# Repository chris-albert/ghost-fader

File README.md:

# Ghost Fader

USB-MIDI-controlled volume and pan for two balanced 1/4" line channels. Balanced in, always-balanced out, one input becomes stereo automatically. Bus-powered Seeed XIAO RP2040 plus a 2x2 gain matrix of PGA2310 attenuators. Revision D: USB only, no DIN jack, no DC jack; the audio side is galvanically isolated from the computer. A TI ISO7762F carries the four control lines and two sense lines across a split in the ground pours, the DC-DC module is the only power path across it, and a 78L05 makes the PGA logic supply on the audio side. About $6 of parts on top of rev C (XIAO RP2040, Traco TBA 2-0522).

The full schematic package (block diagram, five sheets, level budget, USB power budget, MIDI map, build order) is published at https://chris-albert.github.io/ghost-fader/ (source: `docs/index.html`). This file is the short version.

## Signal chain

```
J1/J2 TRS in -> THAT 1246 (bal->SE, -6 dB) -> 2x PGA2310 (2x2 matrix, 4 gains)
             -> OPA1642 summers (non-inverting, x2) -> THAT 1646 (SE->bal, +6 dB) -> J3/J4 TRS out
```

- Net gain balanced-to-balanced is 0 dB at PGA code 192. PGA range is +31.5 to -95.5 dB in 0.5 dB steps, plus hard mute.
- A TS plug on an input grounds the ring, so unbalanced sources need no switch. A TS plug on an output is handled by the cross-coupled 1646.
- Plug sense: each input jack's ring-normal contact is pulled up to +5VA by 100 k and read by the XIAO (D0, D1) through the isolator. Tip-normal is grounded.
- Matrix: U3 carries the direct paths (L->L, R->R), U4 the cross paths (L->R, R->L). Mono mode pans the L input across both outputs with a constant-power law; stereo mode uses balance.

## Power

Everything runs from the USB cable. There is no external power supply, DC jack or wall adapter. The XIAO's 5V pin is USB VBUS straight through, so it exports the bus 5 V. That feeds PS1, a small isolated 5 V -> +/-12 V DC-DC converter soldered to the board (Traco TBA 2-0522, 2 W, SIP-7), for the analog stages. The PGA2310 logic supply and the audio side of the isolator run on +5VA, made from +12 V by U10, a 78L05, so nothing on the audio side references the USB ground.

PS1 is unregulated: the rails follow the USB voltage and the load, from about +/-11 V on a sagging port to about +/-14 V at 5.25 V and light load. Every part on the rails is rated for that (the PGA2310 absolute maximum is 16 V, which is why the +/-15 V TBA 2-0523 is not used). Headroom at +/-12 V is about 2 dB less than on +/-15 V: the output driver clips near +22 dBu instead of +24. Total rail capacitance, about 120 uF per rail, stays under the 220 uF the TBA 2 allows.

| Load | Current at 5 V |
|---|---|
| XIAO RP2040, isolator side 1 | ~35 mA |
| PS1 delivering ~55 mA on +12 V (analog ~40 mA plus U10 ~15 mA) and ~40 mA on -12 V, at ~80 % | ~230 mA |
| LED | ~2 mA |
| Total | ~265 mA typical, ~330 mA worst case |

USB 2.0 ports allow 500 mA; USB 3 / USB-C ports allow 900 mA or more. Use a real port or a powered hub and a data cable (not charge-only).

Ground: there are two. GND_USB is the XIAO, its USB-C shell, the DIP switch, the LED, the ferrite, the reservoir cap, the isolator's side 1 and the DC-DC input. GND is everything audio, the PGA logic, the isolator's side 2 and the DC-DC output. They meet only through C45, a 1 nF cap that gives the converter's switching noise a local return so it does not radiate as common mode, and R17, 1 M, which stops the audio side drifting when nothing is plugged in. So the audio ground follows whatever gear is plugged into the jacks, the way a transformer-isolated DI does, and the computer's ground noise never enters the box. The isolator is the F (fail-safe low) part: when the XIAO is unpowered its outputs sit low, so the PGAs stay muted until the firmware is up.

For that to hold in the box, the XIAO's USB-C shell must not touch the enclosure: the enclosure belongs to the audio ground (bond it to the jack sleeves or to the PS1 Common pad with a wire, since the NRJ6HF bushings are plastic), so use a plastic bezel or a clearance cutout for the USB-C, not a metal-to-metal fit.

## XIAO RP2040 pins

| Pin | Signal |
|---|---|
| USB-C | MIDI in (class-compliant, TinyUSB) and 5 V in |
| 5V | USB 5 V out to FB1, PS1 |
| 3V3 | Isolator side 1 (U8 VCC1) |
| D0, D1 (GP26, GP27) | SENSE_L, SENSE_R through U8 (100 k pull-ups to +5VA on the audio side, internal pull-up off) |
| D2-D5 (GP28, GP29, GP6, GP7) | MIDI channel DIP, INPUT_PULLUP |
| D6 (GP0) | /MUTE to both PGA2310 through U8 (10 k pull-down on the PGA side mutes at boot) |
| D7 (GP1) | /CS through U8 |
| D8 (GP2, SCK) | SCLK through U8 |
| D9 (GP4, the MISO pin) | MIDI activity LED. Nothing comes back from the PGAs, so bit-bang the frame or leave SPI RX unassigned |
| D10 (GP3, MOSI) | SDI of U3 through U8; U3 SDO chains to U4 SDI |

The schematic symbol numbers the XIAO's 14 pins as Seeed's footprint does: 1-7 down the left row from the USB end (D0-D6), 8-14 up the right row (D7-D10, 3V3, GND, 5V).

SPI frame: 32 bits per update, U4's 16-bit word first, then U3's. Each word is the right-channel byte then the left. Code = 192 + 2 * dB, 0 = mute.

## MIDI map (proposed)

| CC | Function |
|---|---|
| 7 | Volume, 127 = 0 dB, 40*log10(v/127) dB |
| 10 | Pan (mono: constant power; stereo: balance) |
| 14, 15 | L / R input trim, +/-12 dB, 64 = 0 dB |
| 85 | Mono sum on/off |
| 120 | Hard mute |

## Parts list

Prices are approximate single-piece USD.

| Ref | Qty | Part | Description | ~$ ea | Notes |
|---|---|---|---|---|---|
| U1, U2 | 2 | THAT 1246S08 | Balanced line receiver, -6 dB | 5.50 | Alt: TI INA137 |
| U3, U4 | 2 | TI PGA2310PA | Stereo volume control, +/-15 V, SPI, DIP-16 | 11.00 | PGA2310UA for SOIC. Not PGA2311 |
| U5 | 1 | TI OPA2134PA | Dual JFET op-amp, DIP-8 | 4.00 | Alt: NE5532P |
| U6, U7 | 2 | THAT 1646S08 | Cross-coupled balanced driver, +6 dB | 5.50 | Alt: TI DRV134 |
| U8 | 1 | TI ISO7762FDW | 6-channel digital isolator, 4 forward / 2 reverse, fail-safe low, SOIC-16W | 4.50 | Not the plain ISO7762 (defaults high, which would unmute the PGAs while the XIAO boots) |
| U9 | 1 | Seeed XIAO RP2040 | MCU with USB-C, class-compliant USB MIDI via TinyUSB | 5.00 | On header pins. Its 5V pin is USB VBUS and feeds the board |
| U10 | 1 | L78L05 | 5 V 100 mA regulator, TO-92, from +12 V | 0.30 | Makes +5VA on the audio side for the PGA logic and U8 side 2, about 15 mA |
| PS1 | 1 | Traco TBA 2-0522 | Board-mounted isolated DC-DC, 4.5-5.5 V in, +/-12 V 80 mA, 2 W, unregulated, SIP-7 | 5.00 | Fed from USB 5 V, not an external supply. Any industry-standard SIP-7 2 W +/-12 V module (Mornsun B0512, RECOM RB-0512D) has the same pinout. Not a +/-15 V part: unregulated rails would pass the PGA2310's 16 V maximum at light load |
| FB1 | 1 | Ferrite bead 600 R @ 100 MHz, >=1 A | Keeps switching noise off USB | 0.20 | |
| J1-J4 | 4 | Neutrik NRJ6HF | 1/4" TRS PCB jack, T and R switching | 3.00 | Switch contacts used on J1, J2 only |
| L1, L2 | 2 | 10 uH, >=300 mA | Rail filters | 0.40 | |
| SW1 | 1 | 4-way DIP | MIDI channel | 0.80 | |
| LED1 | 1 | 3 mm LED | Activity | 0.15 | |
| C3-C6, C17-C20 | 8 | 10 uF non-polar | C3-C6 coupling into PGA inputs, C17-C20 THAT 1646 sense caps | 0.40 | Nichicon UES |
| C1, C2, C7-C10, C15, C16 | 8 | 100 pF C0G | RF caps at every jack tip and ring | 0.10 | |
| C11 | 1 | 47 uF 10 V low-ESR | USB-side reservoir | 0.25 | |
| C12, C13 | 2 | 100 uF 25 V | Rail filters | 0.25 | |
| C14 | 1 | 10 uF | +5VA logic rail | 0.10 | |
| C21-C39, C44 | 20 | 100 nF X7R | One per supply pin; C37/C38 at U10, C39/C44 at U8 | 0.05 | |
| C45 | 1 | 1 nF 1 kV ceramic | Ground barrier cap, GND to GND_USB | 0.15 | Straddles the pour gap at PS1 |
| C40-C43 | 4 | 10 uF 25 V | +/-12 V bulk, input end and output end | 0.10 | |
| R2-R9 | 8 | 10 k 1% | Summing and feedback | 0.05 | |
| R10-R13 | 4 | 10 R | Output build-out | 0.05 | |
| R1, R14 | 2 | 100 k | Plug-sense pull-ups to +5VA | 0.05 | 100 k, not 1 M: U8's inputs leak up to 10 uA |
| R15, R16 | 2 | 10 k, 1 k | Mute pull-down, LED | 0.05 | |
| R17 | 1 | 1 M | Ground barrier bleed, GND to GND_USB | 0.05 | Straddles the pour gap |
| CABLE | 1 | USB A/C to USB-C data cable | Short and thick | 3.00 | |
| ENC | 1 | Hammond 1590BB | Die-cast enclosure | 12.00 | |
| PCB | 1 | 2-layer 108 x 80 mm | Gerbers in `hardware/gerbers/` | 10.00 | Corner notches clear the 1590BB lid-screw bosses |

Estimated total: about $116 per unit, or about $106 with the narrow board in a printed box instead of the 1590BB. Cost-down variant with one PGA2310 and a DG419 routing switch instead of the matrix: about $90, loses cross-feed and mono-sum.

## Full schematic

`hardware/kicad/` is a KiCad 9 project: root sheet plus input, matrix, output, control and power sheets, with a project symbol library (THAT 1246/1646, PGA2310, OPA2134, XIAO RP2040, TBA 2, ISO7762F, 78L05, the GND_USB power symbol) and a footprint for the XIAO on header pins; the TBA 2, the isolator and the regulator use KiCad's stock footprints. ERC passes with zero violations and the netlist (61 nets, 263 pins) has been checked pin-for-pin against `hardware/kicad/tools/check.py`. `bom.csv` is the KiCad BOM export. Rendered sheets and a PDF are in `docs/schematic/` and on the published page.

Every part has a footprint; the jacks use KiCad's stock Neutrik NRJ6HF horizontal footprint, whose pad names match the symbol. The schematic is generated by `hardware/kicad/tools/gen.py`; edit it in KiCad directly from here on, or edit the generator and rerun it (it needs KiCad's stock symbol libraries at the macOS install path).

## PCB

`hardware/kicad/ghost-fader.kicad_pcb` is a routed 2-layer board, 108 x 80 mm, DRC clean against the schematic (the only warnings are the jack noses' and the USB-C shell's silkscreen crossing the board edge, which is inherent to the footprints). Gerbers, Excellon drill file and drill map are in `hardware/gerbers/` and zipped as `hardware/ghost-fader-gerbers.zip`; upload the zip as-is to JLCPCB, PCBWay or OSH Park (2 layers, 1.6 mm, any finish). Renders are in `docs/pcb/` and on the published page.

Layout, rear edge at the top:

- The four jacks sit along one long edge, IN L, IN R, OUT L, OUT R at 19, 39, 68 and 90 mm from the left edge. Their threaded noses stick 1.5 mm past the board edge so the panel nuts have thread to bite. Drill the enclosure wall on those centres.
- Signal flows down and around: jacks -> RF caps -> THAT 1246 receivers (rotated so the inputs face the jacks) -> coupling caps -> the two PGA2310s side by side, analog pins facing up and SPI pins facing the XIAO -> OPA2134 summer and its resistors on the right -> THAT 1646 drivers under the output jacks with their sense caps and build-outs.
- The front-left corner is the USB ground island: the XIAO with its USB-C face flush with the front edge (cut a slot in the front wall for the plug, and keep the shell off the metal), the DIP switch to its right, the LED and its resistor in the left column, the ferrite and reservoir cap, and the input end of the DC-DC. The isolator U8 lies across the top edge of the island with its USB row inside and its audio row outside; PS1 lies across the island's right edge the same way. The barrier parts C45 and R17 straddle the gap in the left column. The 78L05, rail filters and the rest of the power section are front-centre on the audio side, the far corner from the input receivers.
- Every decoupling cap is within a few mm of its supply pin. The +/-12 V bulk pairs are at the input end (C40/C41, between J2 and J3) and the output end (C42/C43, right edge).
- Two ground pours on both layers, audio and USB, separated by a 2 mm gap with no copper. A rule area over the gap keeps the router out, and only U8, PS1, C45 and R17 cross it; a script check confirms no track or via enters the gap. Each pour is stitched by the ground tracks the router laid first, so the schematic's "star at PS1 COM" becomes a plane on the audio side. Power nets are 0.6 mm tracks, signals 0.3 mm, 0.25 mm clearance; anyone can fab it.
- The board is held by the four jack nuts. The corners are notched 7.5 x 6.5 mm to clear the 1590BB lid-screw bosses. Check fit against the actual box before ordering: the inside is about 112 x 86 mm at the base, so there is 2 to 3 mm each way.

The LED is a through-hole 3 mm on the left edge near the front corner; bend it out through a hole in the left wall, or toward the front panel, or fit a light pipe. To regenerate the board from the schematic (placement is a table in `tools/build_pcb.py`, routing is Freerouting):

```
cd hardware/kicad
kicad-cli sch export netlist --format kicadsexpr -o /tmp/gf.net ghost-fader.kicad_sch
<KiCad python3> tools/build_pcb.py /tmp/gf.net          # placement, outline, pours, rules
<KiCad python3> tools/route.py ghost-fader.kicad_pcb <freerouting launcher or jar>
kicad-cli pcb drc --severity-all --schematic-parity -o /tmp/drc.rpt ghost-fader.kicad_pcb
```

`<KiCad python3>` is the interpreter bundled with KiCad (on macOS `/Applications/KiCad/KiCad.app/Contents/Frameworks/Python.framework/Versions/Current/bin/python3`), which has the `pcbnew` module. Freerouting 1.9 was used; 2.4 routes the same board but writes an empty session file from the command line.

## Narrow in-line PCB

`hardware/kicad/ghost-fader-narrow.kicad_pcb` is the same schematic on a second, independent board shaped for a signal chain: 207 x 38 mm, inputs on the right end, outputs on the left, the XIAO's USB-C out of the middle of the rear long edge, so the box sits in-line like a pedal. It is as narrow as two side-by-side jacks allow: the NRJ6HF jacks sit on an 18 mm pitch (34.8 mm) plus edge clearance. The XIAO (21 mm long) lies across the board with its USB-C at the rear edge. It needs a 3D-printed box: about 40 x 210 mm inside, a ledge under the long board edges, two jack holes in each end wall on the jack centres (10 and 28 mm from the rear edge of the board, at the NRJ6HF bushing height), a USB-C slot and a 3 mm LED hole in the rear wall. No mounting holes; the four jack nuts hold the board. Routed, DRC clean against the schematic (the same jack-nose silkscreen warnings as the main board), 0.6 mm power tracks, 0.3 mm signals, split ground pours both sides. The USB ground island is a pocket on the rear edge, x 104 to 141 mm by 28 mm deep, holding the XIAO, LED, DIP switch, ferrite and reservoir; the audio ground wraps under it so the rails and audio pass from the input end to the output end. U8 straddles the pocket's left wall, PS1 its right wall. Gerbers in `hardware/gerbers-narrow/` and `hardware/ghost-fader-narrow-gerbers.zip`; renders in `docs/pcb-narrow/`. The 1590BB board above is unchanged.

Everything runs in columns along the length, left to right: output jacks, RF caps, drivers with their sense caps stacked, build-outs and 100n, summer with its resistors, coupling caps, the two PGA2310s stacked across the board with their SPI rows facing each other, the isolator, the LED and XIAO, DIP switch, ferrite and reservoir over the barrier parts and +/-12 V bulk caps, DC-DC, 78L05 and rail filters, receivers with the sense pull-ups, bulk caps, RF caps, input jacks. The LED sits at the rear edge just left of the XIAO, about 107 mm from the left end. Most reference labels sit on the part bodies because there is no room beside them; they read on the bare board. Parts come within 1 mm of the long edges, so give the printed walls clearance above the board edge.

To regenerate: same steps as above with `tools/build_pcb_narrow.py` in place of `tools/build_pcb.py` and `ghost-fader-narrow.kicad_pcb` as the board.

## Notes

- The overview sheets label IC pins by function. The KiCad schematic in `hardware/kicad/` has the real pin numbers and is the one to lay out from.
- The PGAs are driven at 5 V by the isolator's outputs. Never route a PGA SDO (5 V) back toward the XIAO: the RP2040 is not 5 V tolerant, and nothing crosses U8 in that direction except the two sense lines.
- Ground is two pours on both layers with a 2 mm gap; the DC-DC is at the far end of the board from the input receivers.

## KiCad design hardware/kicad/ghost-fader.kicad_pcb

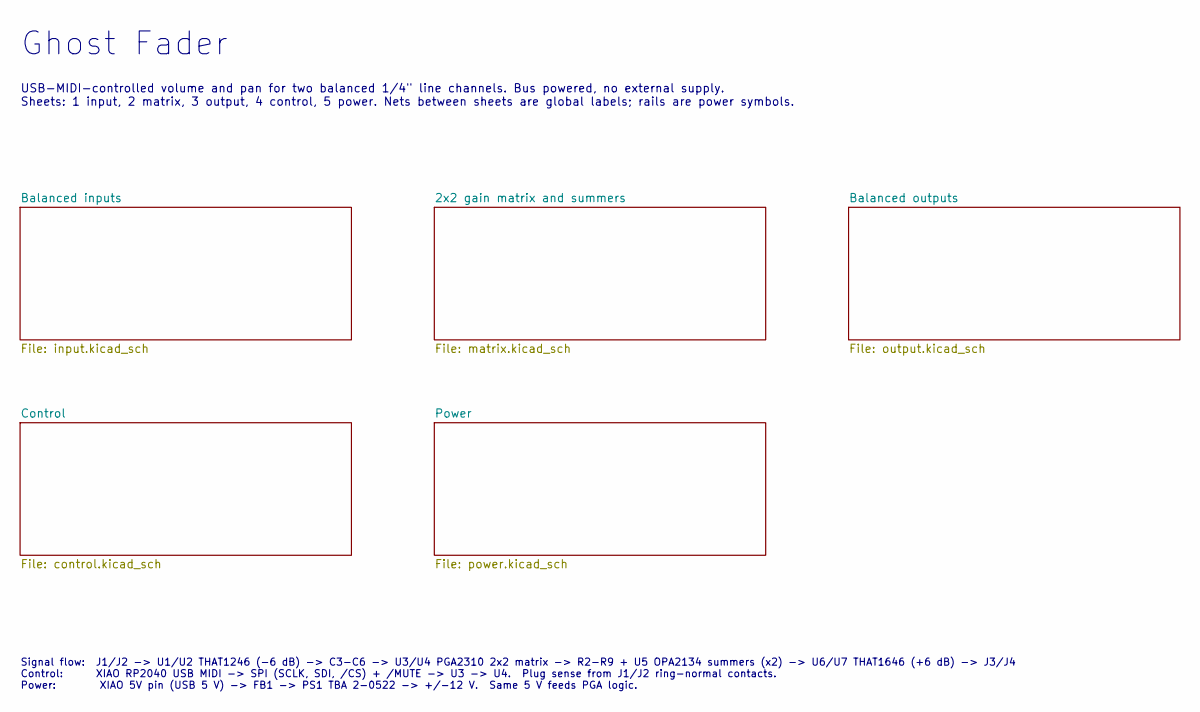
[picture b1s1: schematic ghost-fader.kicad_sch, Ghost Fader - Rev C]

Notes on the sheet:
Ghost Fader
USB-MIDI-controlled volume and pan for two balanced 1/4" line channels. Bus powered, no external supply. Sheets: 1 input, 2 matrix, 3 output, 4 control, 5 power. Nets between sheets are global labels; rails are power symbols.
Signal flow: J1/J2 -> U1/U2 THAT1246 (-6 dB) -> C3-C6 -> U3/U4 PGA2310 2x2 matrix -> R2-R9 + U5 OPA2134 summers (x2) -> U6/U7 THAT1646 (+6 dB) -> J3/J4 Control: XIAO RP2040 USB MIDI -> SPI (SCLK, SDI, /CS) + /MUTE -> U3 -> U4. Plug sense from J1/J2 ring-normal contacts. Power: XIAO 5V pin (USB 5 V)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

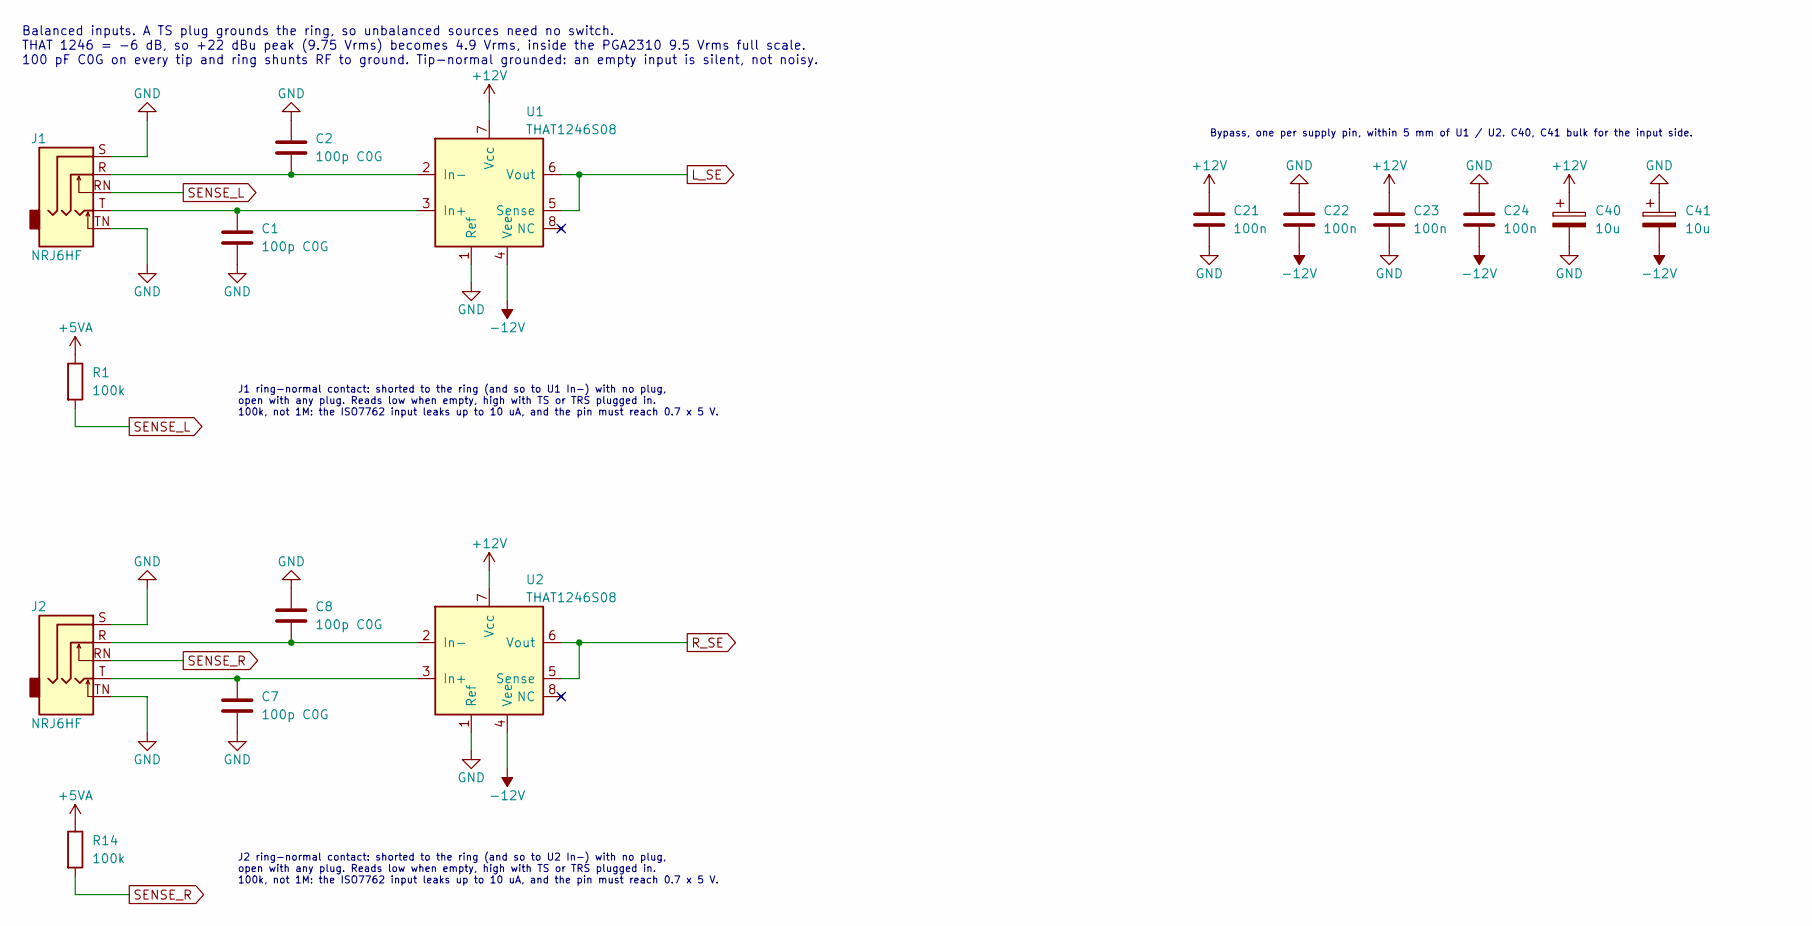
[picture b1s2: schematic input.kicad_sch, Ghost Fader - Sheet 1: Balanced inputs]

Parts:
C1, C2, C7, C8: 100p C0G; C_Disc_D5.0mm_W2.5mm_P5.00mm
C21, C22, C23, C24: 100n; C_Disc_D5.0mm_W2.5mm_P5.00mm
C40, C41: 10u; CP_Radial_D6.3mm_P2.50mm
J1, J2: NRJ6HF; Jack_6.35mm_Neutrik_NRJ6HF_Horizontal
R1, R14: 100k; R_Axial_DIN0207_L6.3mm_D2.5mm_P10.16mm_Horizontal
U1, U2: THAT1246S08; SOIC-8_3.9x4.9mm_P1.27mm

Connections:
+5VA: R1.1, R14.1; also elsewhere on the board
+12V: C21.1, C23.1, C40.1, U1.7 (Vcc), U2.7 (Vcc); also elsewhere on the board
-12V: C22.2, C24.2, C41.2, U1.4 (Vee), U2.4 (Vee); also elsewhere on the board
L_SE: U1.5 (Sense), U1.6 (Vout); also elsewhere on the board
unnamed: C1.1, J1.T, U1.3 (In+)
unnamed: C2.2, J1.R, U1.2 (In-)
unnamed: C7.1, J2.T, U2.3 (In+)
unnamed: C8.2, J2.R, U2.2 (In-)
R_SE: U2.5 (Sense), U2.6 (Vout); also elsewhere on the board
SENSE_L: J1.RN, R1.2; also elsewhere on the board
SENSE_R: J2.RN, R14.2; also elsewhere on the board

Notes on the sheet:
J1 ring-normal contact: shorted to the ring (and so to U1 In-) with no plug, open with any plug. Reads low when empty, high with TS or TRS plugged in. 100k, not 1M: the ISO7762 input leaks up to 10 uA, and the pin must reach 0.7 x 5 V.
J2 ring-normal contact: shorted to the ring (and so to U2 In-) with no plug, open with any plug. Reads low when empty, high with TS or TRS plugged in. 100k, not 1M: the ISO7762 input leaks up to 10 uA, and the pin must reach 0.7 x 5 V.
Balanced inputs. A TS plug grounds the ring, so unbalanced sources need no switch. THAT 1246 = -6 dB, so +22 dBu peak (9.75 Vrms) becomes 4.9 Vrms, inside the PGA2310 9.5 Vrms full scale. 100 pF C0G on every tip and ring shunts RF to ground. Tip-normal grounded: an empty input is silent, not noisy.
Bypass, one per supply pin, within 5 mm of U1 / U2. C40, C41 bulk for the input side.

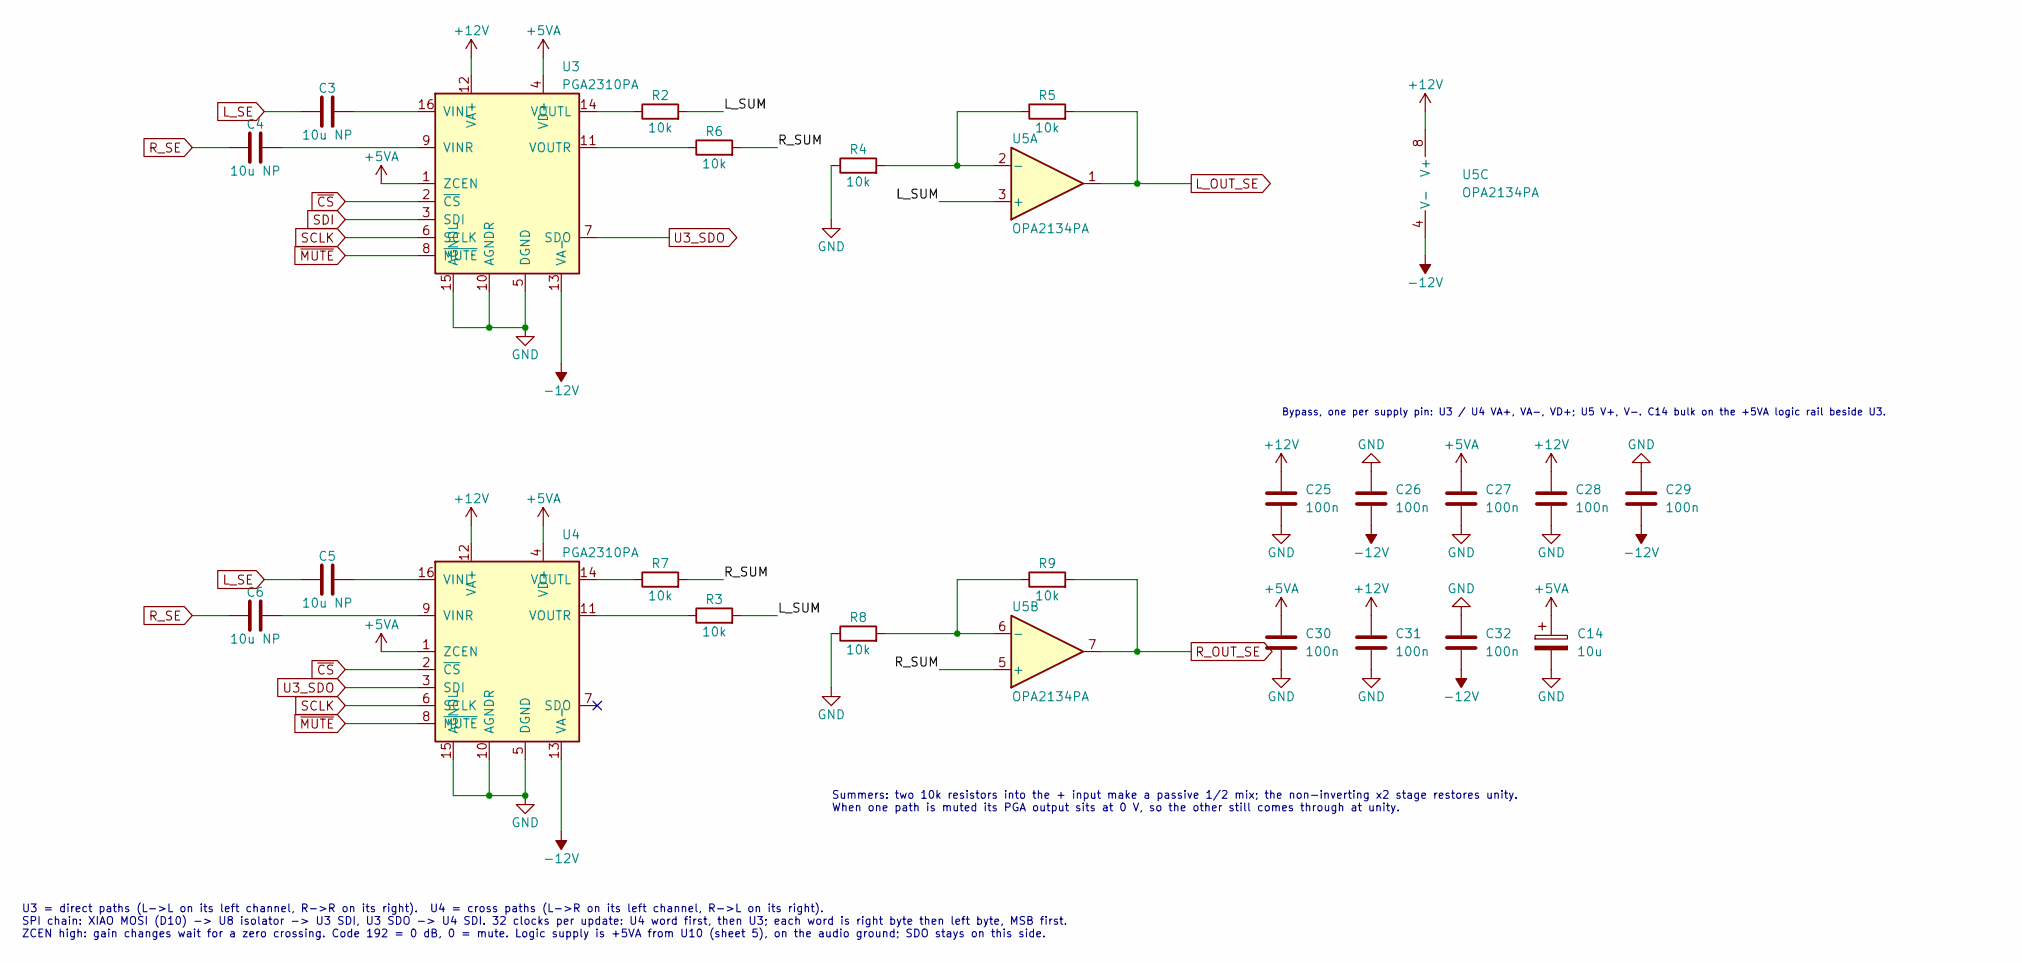
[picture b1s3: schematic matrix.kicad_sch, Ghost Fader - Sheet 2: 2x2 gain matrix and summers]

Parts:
C3, C4, C5, C6: 10u NP; CP_Radial_D5.0mm_P2.50mm
C14: 10u; CP_Radial_D6.3mm_P2.50mm
C25, C26, C27, C28, C29, C30, C31, C32: 100n; C_Disc_D5.0mm_W2.5mm_P5.00mm
R2, R3, R4, R5, R6, R7, R8, R9: 10k; R_Axial_DIN0207_L6.3mm_D2.5mm_P10.16mm_Horizontal
U3, U4: PGA2310PA; DIP-16_W7.62mm
U5: OPA2134PA; DIP-8_W7.62mm

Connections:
+5VA: C14.1, C27.1, C30.1, U3.1 (ZCEN), U3.4 (VD+), U4.1 (ZCEN), U4.4 (VD+); also elsewhere on the board
+12V: C25.1, C28.1, C31.1, U3.12 (VA+), U4.12 (VA+), U5.8 (V+); also elsewhere on the board
-12V: C26.2, C29.2, C32.2, U3.13 (VA-), U4.13 (VA-), U5.4 (V-); also elsewhere on the board
/2x2 gain matrix and summers/L_SUM: R2.2, R3.2, U5.3 (+)
/2x2 gain matrix and summers/R_SUM: R6.2, R7.2, U5.5 (+)
L_OUT_SE: R5.2, U5.1; also elsewhere on the board
L_SE: C3.1, C5.1; also elsewhere on the board
unnamed: C3.2, U3.16 (VINL)
unnamed: C4.2, U3.9 (VINR)
unnamed: R2.1, U3.14 (VOUTL)
unnamed: R6.1, U3.11 (VOUTR)
unnamed: C5.2, U4.16 (VINL)
unnamed: C6.2, U4.9 (VINR)
unnamed: R7.1, U4.14 (VOUTL)
unnamed: R3.1, U4.11 (VOUTR)
unnamed: R4.2, R5.1, U5.2 (-)
unnamed: R8.2, R9.1, U5.6 (-)
R_OUT_SE: R9.2, U5.7; also elsewhere on the board
R_SE: C4.1, C6.1; also elsewhere on the board
SCLK: U3.6 (SCLK), U4.6 (SCLK); also elsewhere on the board
SDI: U3.3 (SDI); also elsewhere on the board
U3_SDO: U3.7 (SDO), U4.3 (SDI)
~CS: U3.2 (~CS), U4.2 (~CS); also elsewhere on the board
~MUTE: U3.8 (~MUTE), U4.8 (~MUTE); also elsewhere on the board

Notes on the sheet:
U3 = direct paths (L->L on its left channel, R->R on its right). U4 = cross paths (L->R on its left channel, R->L on its right). SPI chain: XIAO MOSI (D10) -> U8 isolator -> U3 SDI, U3 SDO -> U4 SDI. 32 clocks per update: U4 word first, then U3; each word is right byte then left byte, MSB first. ZC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
Summers: two 10k resistors into the + input make a passive 1/2 mix; the non-inverting x2 stage restores unity. When one path is muted its PGA output sits at 0 V, so the other still comes through at unity.
Bypass, one per supply pin: U3 / U4 VA+, VA-, VD+; U5 V+, V-. C14 bulk on the +5VA logic rail beside U3.

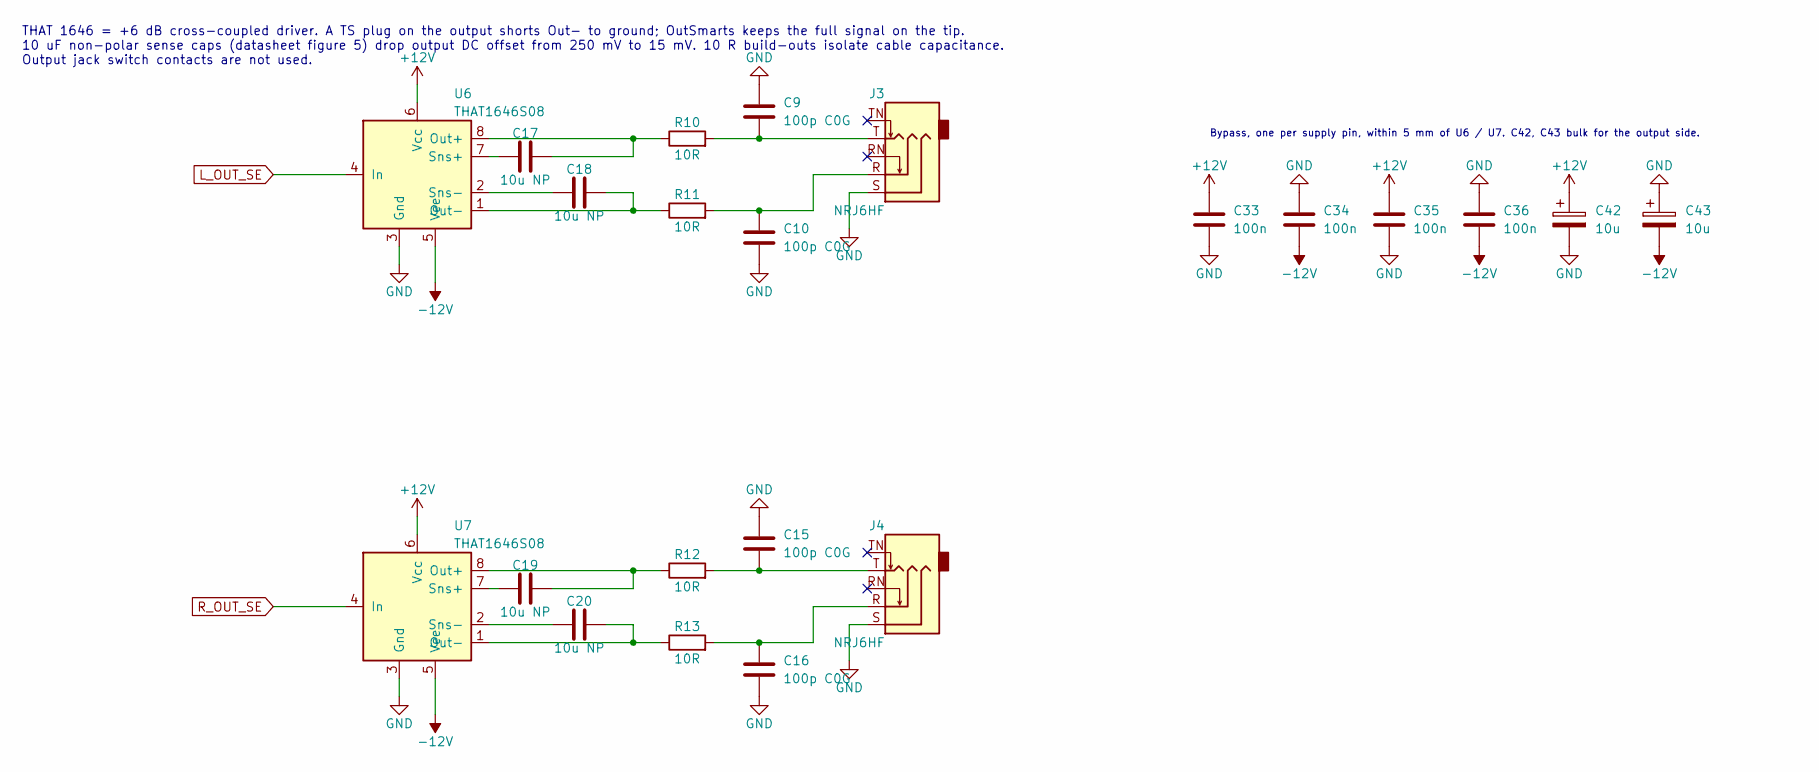
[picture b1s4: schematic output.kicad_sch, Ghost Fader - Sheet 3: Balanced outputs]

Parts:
C9, C10, C15, C16: 100p C0G; C_Disc_D5.0mm_W2.5mm_P5.00mm
C17, C18, C19, C20: 10u NP; CP_Radial_D5.0mm_P2.50mm
C33, C34, C35, C36: 100n; C_Disc_D5.0mm_W2.5mm_P5.00mm
C42, C43: 10u; CP_Radial_D6.3mm_P2.50mm
J3, J4: NRJ6HF; Jack_6.35mm_Neutrik_NRJ6HF_Horizontal
R10, R11, R12, R13: 10R; R_Axial_DIN0207_L6.3mm_D2.5mm_P10.16mm_Horizontal
U6, U7: THAT1646S08; SOIC-8_3.9x4.9mm_P1.27mm

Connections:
+12V: C33.1, C35.1, C42.1, U6.6 (Vcc), U7.6 (Vcc); also elsewhere on the board
-12V: C34.2, C36.2, C43.2, U6.5 (Vee), U7.5 (Vee); also elsewhere on the board
L_OUT_SE: U6.4 (In); also elsewhere on the board
unnamed: C9.2, J3.T, R10.2
unnamed: C10.1, J3.R, R11.2
unnamed: C15.2, J4.T, R12.2
unnamed: C16.1, J4.R, R13.2
unnamed: C17.2, R10.1, U6.8 (Out+)
unnamed: C18.2, R11.1, U6.1 (Out-)
unnamed: C17.1, U6.7 (Sns+)
unnamed: C18.1, U6.2 (Sns-)
unnamed: C19.2, R12.1, U7.8 (Out+)
unnamed: C20.2, R13.1, U7.1 (Out-)
unnamed: C19.1, U7.7 (Sns+)
unnamed: C20.1, U7.2 (Sns-)
R_OUT_SE: U7.4 (In); also elsewhere on the board

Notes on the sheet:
THAT 1646 = +6 dB cross-coupled driver. A TS plug on the output shorts Out- to ground; OutSmarts keeps the full signal on the tip. 10 uF non-polar sense caps (datasheet figure 5) drop output DC offset from 250 mV to 15 mV. 10 R build-outs isolate cable capacitance. Output jack switch contacts are n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
Bypass, one per supply pin, within 5 mm of U6 / U7. C42, C43 bulk for the output side.

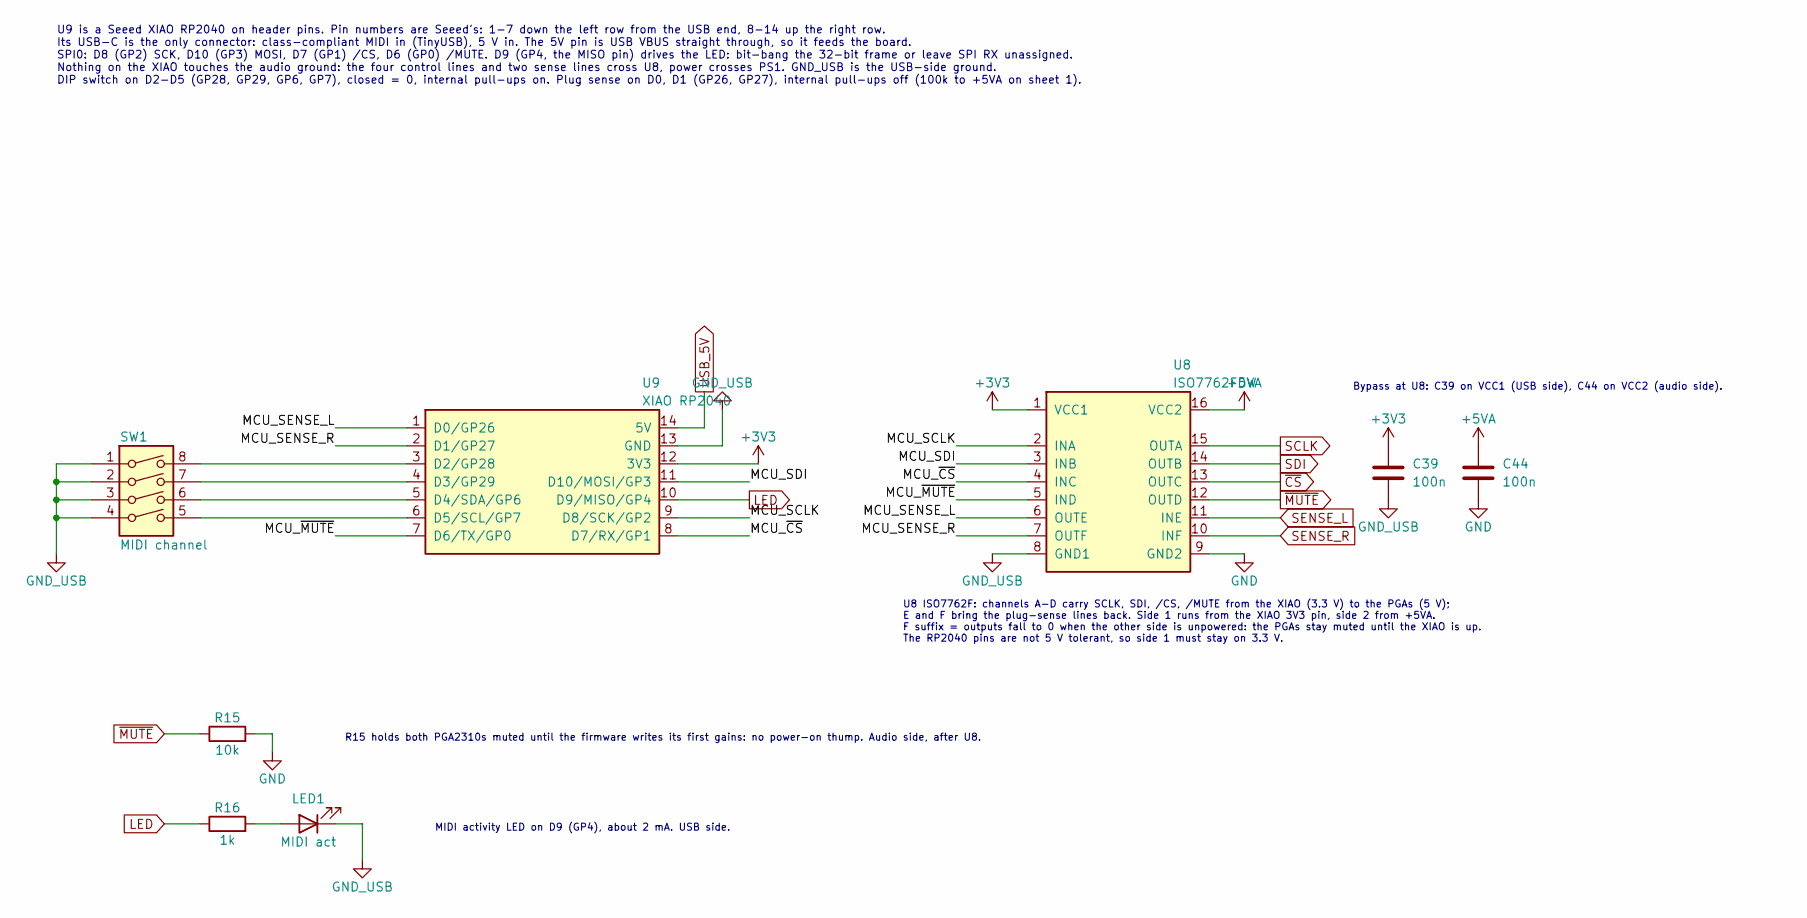
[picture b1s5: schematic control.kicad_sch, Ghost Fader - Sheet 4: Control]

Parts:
C39, C44: 100n; C_Disc_D5.0mm_W2.5mm_P5.00mm
LED1: MIDI act; LED_D3.0mm
R15: 10k; R_Axial_DIN0207_L6.3mm_D2.5mm_P10.16mm_Horizontal
R16: 1k; R_Axial_DIN0207_L6.3mm_D2.5mm_P10.16mm_Horizontal
SW1: MIDI channel; SW_DIP_SPSTx04_Slide_6.7x11.72mm_W7.62mm_P2.54mm_LowProfile
U8: ISO7762FDW; SOIC-16W_7.5x10.3mm_P1.27mm
U9: XIAO RP2040; XIAO_RP2040_THT

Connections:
+3V3: C39.1, U8.1 (VCC1), U9.12 (3V3)
+5VA: C44.1, U8.16 (VCC2); also elsewhere on the board
/Control/MCU_SCLK: U8.2 (INA), U9.9 (D8/SCK/GP2)
/Control/MCU_SDI: U8.3 (INB), U9.11 (D10/MOSI/GP3)
/Control/MCU_SENSE_L: U8.6 (OUTE), U9.1 (D0/GP26)
/Control/MCU_SENSE_R: U8.7 (OUTF), U9.2 (D1/GP27)
/Control/MCU_~CS: U8.4 (INC), U9.8 (D7/RX/GP1)
/Control/MCU_~MUTE: U8.5 (IND), U9.7 (D6/TX/GP0)
LED: R16.1, U9.10 (D9/MISO/GP4)
unnamed: LED1.2 (A), R16.2
unnamed: SW1.8, U9.3 (D2/GP28)
unnamed: SW1.7, U9.4 (D3/GP29)
unnamed: SW1.6, U9.5 (D4/SDA/GP6)
unnamed: SW1.5, U9.6 (D5/SCL/GP7)
SCLK: U8.15 (OUTA); also elsewhere on the board
SDI: U8.14 (OUTB); also elsewhere on the board
SENSE_L: U8.11 (INE); also elsewhere on the board
SENSE_R: U8.10 (INF); also elsewhere on the board
USB_5V: U9.14 (5V); also elsewhere on the board
~CS: U8.13 (OUTC); also elsewhere on the board
~MUTE: R15.1, U8.12 (OUTD); also elsewhere on the board

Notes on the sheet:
U8 ISO7762F: channels A-D carry SCLK, SDI, /CS, /MUTE from the XIAO (3.3 V) to the PGAs (5 V); E and F bring the plug-sense lines back. Side 1 runs from the XIAO 3V3 pin, side 2 from +5VA. F suffix = outputs fall to 0 when the other side is unpowered: the PGAs stay muted until the XIAO is up. The R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
Bypass at U8: C39 on VCC1 (USB side), C44 on VCC2 (audio side).
MIDI activity LED on D9 (GP4), about 2 mA. USB side.
R15 holds both PGA2310s muted until the firmware writes its first gains: no power-on thump. Audio side, after U8.
U9 is a Seeed XIAO RP2040 on header pins. Pin numbers are Seeed's: 1-7 down the left row from the USB end, 8-14 up the right row. Its USB-C is the only connector: class-compliant MIDI in (TinyUSB), 5 V in. The 5V pin is USB VBUS straight through, so it feeds the board. SPI0: D8 (GP2) SCK, D10 (GP3)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

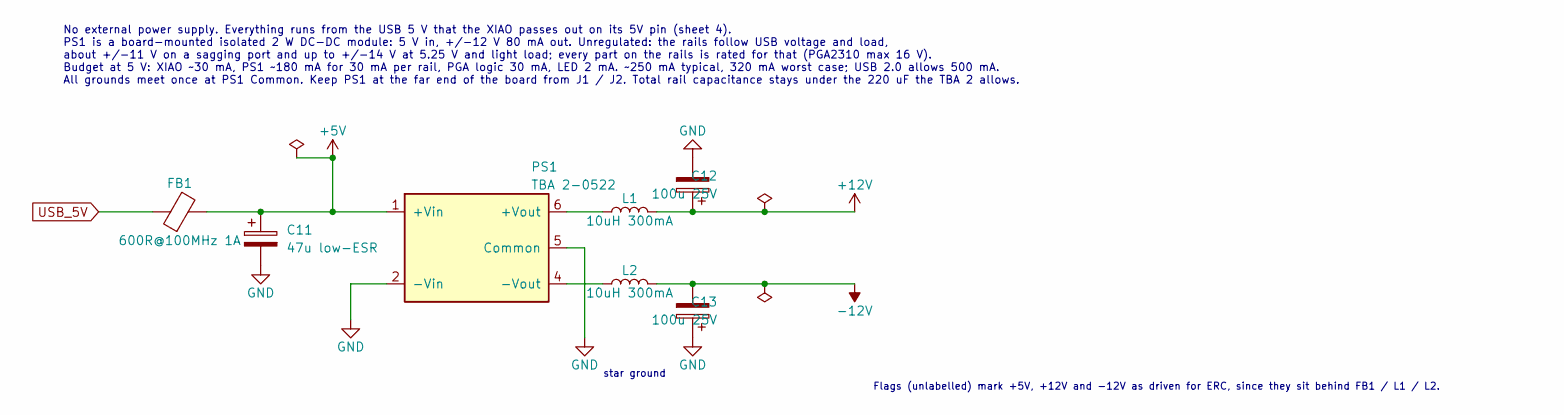
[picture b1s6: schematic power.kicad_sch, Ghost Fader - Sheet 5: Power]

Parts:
C11: 47u low-ESR; CP_Radial_D6.3mm_P2.50mm
C12, C13: 100u 25V; CP_Radial_D6.3mm_P2.50mm
FB1: 600R@100MHz 1A; L_Axial_L7.0mm_D3.3mm_P10.16mm_Horizontal_Fastron_MICC
L1, L2: 10uH 300mA; L_Axial_L7.0mm_D3.3mm_P10.16mm_Horizontal_Fastron_MICC
PS1: TBA 2-0522; Converter_DCDC_TRACO_TBA2-xxxx_Dual_THT

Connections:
+5V: C11.1, FB1.2, PS1.1 (+Vin)
+12V: C12.1, L1.2; also elsewhere on the board
-12V: C13.2, L2.2; also elsewhere on the board
unnamed: L1.1, PS1.6 (+Vout)
unnamed: L2.1, PS1.4 (-Vout)
USB_5V: FB1.1; also elsewhere on the board

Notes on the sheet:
star ground
No external power supply. Everything runs from the USB 5 V that the XIAO passes out on its 5V pin (sheet 4). PS1 is a board-mounted isolated 2 W DC-DC module: 5 V in, +/-12 V 80 mA out. Unregulated: the rails follow USB voltage and load, about +/-11 V on a sagging port and up to +/-14 V at 5.25 V a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
Flags (unlabelled) mark +5V, +12V and -12V as driven for ERC, since they sit behind FB1 / L1 / L2.

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
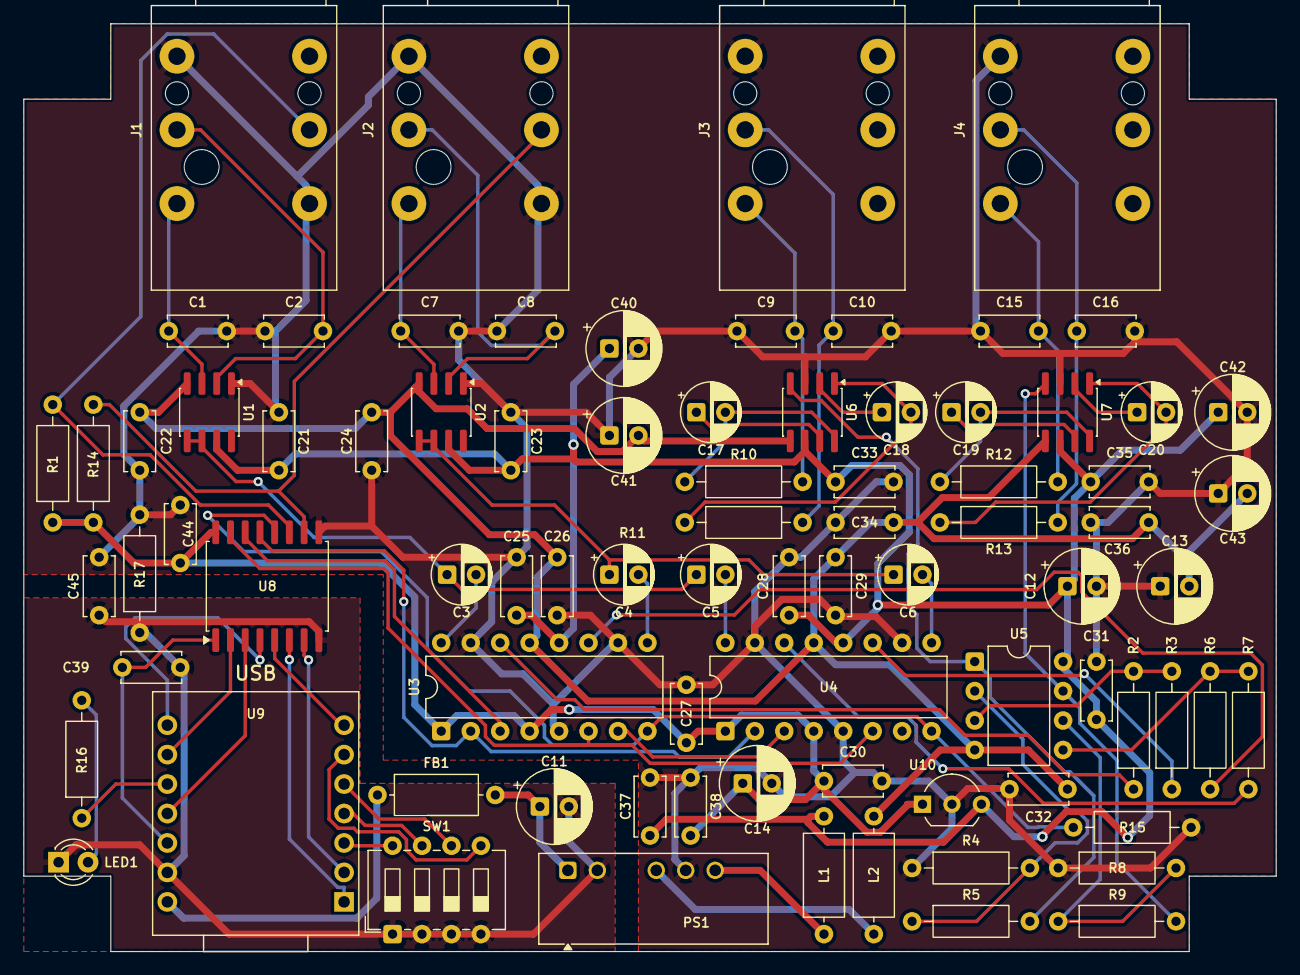
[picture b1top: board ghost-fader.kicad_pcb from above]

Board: 2 copper layers, 108.0 x 80.0 mm, 82 parts (0 on the bottom side), 61 nets.

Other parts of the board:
C37, C38: 100n; C_Disc_D5.0mm_W2.5mm_P5.00mm
C45: 1n 1kV; C_Disc_D5.0mm_W2.5mm_P5.00mm
R17: 1M; R_Axial_DIN0207_L6.3mm_D2.5mm_P10.16mm_Horizontal
U10: L78L05; TO-92_Inline_Wide

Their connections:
+5VA: C38.1, U10.1; also elsewhere on the board
+12V: C37.1, U10.3; also elsewhere on the board

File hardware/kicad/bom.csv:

"Reference","Value","Footprint","QUANTITY"
"C1,C2,C7-C10,C15,C16","100p C0G","Capacitor_THT:C_Disc_D5.0mm_W2.5mm_P5.00mm","8"
"C3-C6,C17-C20","10u NP","Capacitor_THT:CP_Radial_D5.0mm_P2.50mm","8"
"C11","47u low-ESR","Capacitor_THT:CP_Radial_D6.3mm_P2.50mm","1"
"C12,C13","100u 25V","Capacitor_THT:CP_Radial_D6.3mm_P2.50mm","2"
"C14,C40-C43","10u","Capacitor_THT:CP_Radial_D6.3mm_P2.50mm","5"
"C21-C36","100n","Capacitor_THT:C_Disc_D5.0mm_W2.5mm_P5.00mm","16"
"FB1","600R@100MHz 1A","Inductor_THT:L_Axial_L7.0mm_D3.3mm_P10.16mm_Horizontal_Fastron_MICC","1"
"J1-J4","NRJ6HF","Connector_Audio:Jack_6.35mm_Neutrik_NRJ6HF_Horizontal","4"
"L1,L2","10uH 300mA","Inductor_THT:L_Axial_L7.0mm_D3.3mm_P10.16mm_Horizontal_Fastron_MICC","2"
"LED1","MIDI act","LED_THT:LED_D3.0mm","1"
"PS1","TBA 2-0522","Converter_DCDC:Converter_DCDC_TRACO_TBA2-xxxx_Dual_THT","1"
"R1,R14","1M","Resistor_THT:R_Axial_DIN0207_L6.3mm_D2.5mm_P10.16mm_Horizontal","2"
"R2-R9,R15","10k","Resistor_THT:R_Axial_DIN0207_L6.3mm_D2.5mm_P10.16mm_Horizontal","9"
"R10-R13","10R","Resistor_THT:R_Axial_DIN0207_L6.3mm_D2.5mm_P10.16mm_Horizontal","4"
"R16","1k","Resistor_THT:R_Axial_DIN0207_L6.3mm_D2.5mm_P10.16mm_Horizontal","1"
"SW1","MIDI channel","Button_Switch_THT:SW_DIP_SPSTx04_Slide_6.7x11.72mm_W7.62mm_P2.54mm_LowProfile","1"
"U1,U2","THAT1246S08","Package_SO:SOIC-8_3.9x4.9mm_P1.27mm","2"
"U3,U4","PGA2310PA","Package_DIP:DIP-16_W7.62mm","2"
"U5","OPA2134PA","Package_DIP:DIP-8_W7.62mm","1"
"U6,U7","THAT1646S08","Package_SO:SOIC-8_3.9x4.9mm_P1.27mm","2"
"U9","XIAO RP2040","GhostFader:XIAO_RP2040_THT","1"

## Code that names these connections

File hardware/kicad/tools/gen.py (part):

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        u = s.place('GhostFader:PGA2310', ref, 'PGA2310PA', 101.6, uy, fp=FOOTPRINTS['DIP16'])
        # coupling caps into the two inputs
        vinl, vinr = u.p('16'), u.p('9')
        c1 = s.place('Device:C', cl, '10u NP', 76.2, vinl[1], 90, fp=FOOTPRINTS['CNP']); s.wire(c1.p('2'), vinl); s.stub_glabel(c1.p('1'), 'L', 'L_SE', 2)
        c2 = s.place('Device:C', cr, '10u NP', 66.04, vinr[1], 90, fp=FOOTPRINTS['CNP']); s.wire(c2.p('2'), vinr); s.stub_glabel(c2.p('1'), 'L', 'R_SE', 2)
        s.stub_pwr(u.p('1'), 'L', '+5VA', 2)
        s.stub_glabel(u.p('2'), 'L', '~{CS}', 4)
        s.stub_glabel(u.p('3'), 'L', sdi_from, 4)
        s.stub_glabel(u.p('6'), 'L', 'SCLK', 4)
        s.stub_glabel(u.p('8'), 'L', '~{MUTE}', 4)
        if sdo_to: s.stub_glabel(u.p('7'), 'R', sdo_to, 4, 'output')
        else: s.nc(u.p('7'))
        s.stub_pwr(u.p('12'), 'U', '+12V', 1)
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    s = Sheet('control.kicad_sch', 'Ghost Fader - Sheet 4: Control', 'XIAO RP2040, USB MIDI, ISO7762F isolator, plug sense, SPI')
    t = s.place('GhostFader:XIAO_RP2040', 'U9', 'XIAO RP2040', 101.6, 101.6, fp=FOOTPRINTS['XIAO'])
    # left row: D0-D6. Everything on the XIAO is on the USB side (GND_USB); MCU_* nets go through U8.
    s.stub_label(t.p('1'), 'L', 'MCU_SENSE_L', 4)
    s.stub_label(t.p('2'), 'L', 'MCU_SENSE_R', 4)
    sw = s.place('Switch:SW_DIP_x04', 'SW1', 'MIDI channel', 45.72, 104.14, fp=FOOTPRINTS['DIP4'])
    for tp, sp in (('3', '8'), ('4', '7'), ('5', '6'), ('6', '5')):
        assert t.p(tp)[1] == sw.p(sp)[1]
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        s.wire(sw.p(sp), (33.02, sw.p(sp)[1]))
    s.wire((33.02, sw.p('1')[1]), (33.02, sw.p('4')[1] + 5.08))
    s.pwr('GND_USB', 33.02, sw.p('4')[1] + 5.08, 0)
    s.stub_label(t.p('7'), 'L', 'MCU_~{MUTE}', 4)
    # right row, bottom up: D7-D10, 3V3, GND, 5V
    s.stub_label(t.p('8'), 'R', 'MCU_~{CS}', 4)
    s.stub_label(t.p('9'), 'R', 'MCU_SCLK', 4)
    s.stub_glabel(t.p('10'), 'R', 'LED', 4, 'output')
    s.stub_label(t.p('11'), 'R', 'MCU_SDI', 4)
    v33 = t.p('12'); s.wire(v33, (132.08, v33[1])); s.pwr('+3V3', 132.08, v33[1], 0)
    gnd = t.p('13'); s.wire(gnd, (127, gnd[1]), (127, gnd[1] - 5.08)); s.pwr('GND_USB', 127, gnd[1] - 5.08, 180)
    vin = t.p('14'); s.wire(vin, (124.46, vin[1]), (124.46, vin[1] - 5.08)); s.glabel('USB_5V', 124.46, vin[1] - 5.08, 90, 'output')
    # isolator: side 1 (pins 1-8) on the USB ground, side 2 (pins 9-16) on the audio ground
    u = s.place('GhostFader:ISO7762F', 'U8', 'ISO7762FDW', 182.88, 101.6, fp=FOOTPRINTS['SO16W'])
    s.stub_pwr(u.p('1'), 'L', '+3V3', 2)
    s.stub_label(u.p('2'), 'L', 'MCU_SCLK', 4)
    s.stub_label(u.p('3'), 'L', 'MCU_SDI', 4)
    s.stub_label(u.p('4'), 'L', 'MCU_~{CS}', 4)
    s.stub_label(u.p('5'), 'L', 'MCU_~{MUTE}', 4)
    s.stub_label(u.p('6'), 'L', 'MCU_SENSE_L', 4)
    s.stub_label(u.p('7'), 'L', 'MCU_SENSE_R', 4)
    s.stub_pwr(u.p('8'), 'L', 'GND_USB', 2)
    s.stub_pwr(u.p('16'), 'R', '+5VA', 2)
    s.stub_glabel(u.p('15'), 'R', 'SCLK', 4, 'output')
    s.stub_glabel(u.p('14'), 'R', 'SDI', 4, 'output')
    s.stub_glabel(u.p('13'), 'R', '~{CS}', 4, 'output')
    s.stub_glabel(u.p('12'), 'R', '~{MUTE}', 4, 'output')
    s.stub_glabel(u.p('11'), 'R', 'SENSE_L', 4)
    s.stub_glabel(u.p('10'), 'R', 'SENSE_R', 4)
    s.stub_pwr(u.p('9'), 'R', 'GND', 2)
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    # isolator bypass, one per side
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    s.wire(led.p('1'), (76.2, ly), (76.2, ly + 5.08)); s.pwr('GND_USB', 76.2, ly + 5.08, 0)
    s.text('MIDI activity LED on D9 (GP4), about 2 mA. USB side.', 86.36, ly + 1.27, 1.0)
    # mute pull-down snippet (audio side, on the isolated /MUTE net)
    s.glabel('~{MUTE}', 48.26, 137.16, 180);
    r15 = s.place('Device:R', 'R15', '10k', 57.15, 137.16, 90, fp=FOOTPRINTS['R'])
    s.wire((48.26, 137.16), r15.p('1')); s.wire(r15.p('2'), (63.5, 137.16), (63.5, 139.7)); s.pwr('GND', 63.5, 139.7, 0)
    s.text('R15 holds both PGA2310s muted until the firmware writes its first gains: no power-on thump. Audio side, after U8.', 73.66, 138.43, 1.0)
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def build_power():
    s = Sheet('power.kicad_sch', 'Ghost Fader - Sheet 5: Power', 'USB 5 V in, isolated +/-12 V and +5VA, USB ground split from audio ground')
    y = 63.5
    s.glabel('USB_5V', 38.1, y, 180)
    fb = s.place('Device:FerriteBead', 'FB1', '600R@100MHz 1A', 49.53, y, 90, fp=FOOTPRINTS['L'])
    s.wire((38.1, y), fb.p('1'))
    ps = s.place('GhostFader:TBA2_Dual', 'PS1', 'TBA 2-0522', 91.44, y + 5.08, fp=FOOTPRINTS['TBA2'])
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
